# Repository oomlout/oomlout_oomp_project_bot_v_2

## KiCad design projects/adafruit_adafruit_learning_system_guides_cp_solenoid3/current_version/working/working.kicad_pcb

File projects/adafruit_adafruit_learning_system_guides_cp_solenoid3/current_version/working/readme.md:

# adafruit_learning_system_guides
 
## summary 
* id: adafruit_adafruit_learning_system_guides_cp_solenoid3
* user: adafruit
* name: adafruit_learning_system_guides
* board: cp_solenoid3
* repo: https://github.com/adafruit/Adafruit_Learning_System_Guides

* src_file_repo_sch: 
* src_file_repo_sch_link: https://github.com/adafruit/Adafruit_Learning_System_Guides/tree/main/
* full details link: https://github.com/oomlout/oomlout_oomp_project_bot_v_2/tree/main/projects/adafruit_adafruit_learning_system_guides_cp_solenoid3/current_version/working  

## schematic  
  
[schematic (pdf)](working_schematic.pdf) 

## pcb  

[board (pdf)](working.pdf)  

## working_bom
| Id | Designator | Footprint | Quantity | Designation | Supplier and ref |  | None | 
| --- | --- | --- | --- | --- | --- | --- | --- | 
| 1 | D1 | DO41-10 | 1 | 1N4004 |  |  | [''] | 
| 2 | R2 | 0414_15 | 1 | 15M |  |  | [''] | 
| 3 | SOLENOID0,LED0 | B2B-PH-K-S | 2 |  |  |  | [''] | 
| 4 | R1 | 0207_10 | 1 | 10K |  |  | [''] | 
| 5 | Q2 | TO220 | 1 | IRLB8721 |  |  | [''] | 
| 6 | C1 | C025-025X050 | 1 | 82nF |  |  | [''] | 
| 7 | MS1 | FEATHERWING_DIM | 1 | FEATHERWING_NODIM |  |  | [''] | 

## bom_schematic
| Ref | Qnty | Value | Cmp name | Footprint | Description | Vendor | DNP | 
| --- | --- | --- | --- | --- | --- | --- | --- | 
| C1 | 1 | 82nF | C-EU025-025X050 | working:C025-025X050 |  |  |  | 
| D1 | 1 | 1N4004 | 1N4004 | working:DO41-10 |  |  |  | 
| LED0 | 1 | B2B-PH-K-S | B2B-PH-K-S | working:B2B-PH-K-S |  |  |  | 
| MS1 | 1 | FEATHERWING_NODIM | FEATHERWING_NODIM | working:FEATHERWING_DIM |  |  |  | 
| Q2 | 1 | IRF510 | IRF510 | working:TO220 |  |  |  | 
| R1 | 1 | 10K | R-EU_0207/10 | working:0207_10 |  |  |  | 
| R2 | 1 | 15M | R-EU_0414/15 | working:0414_15 |  |  |  | 
| SOLENOID0 | 1 | B2B-PH-K-S | B2B-PH-K-S | working:B2B-PH-K-S |  |  |  |

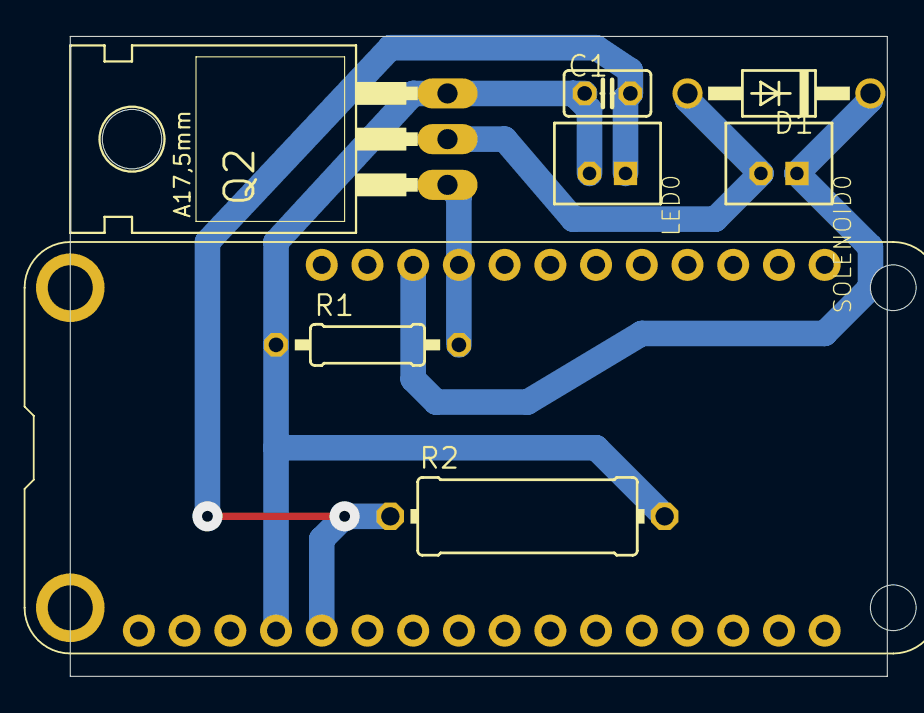
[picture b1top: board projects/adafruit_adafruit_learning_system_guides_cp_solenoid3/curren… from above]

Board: 2 copper layers, 45.4 x 35.5 mm, 8 parts (0 on the bottom side), 5 nets.

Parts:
C1: 82nF; C025-025X050
D1: 1N4004; DO41-10
LED0: B2B-PH-K-S
MS1: FEATHERWING_NODIM; FEATHERWING_DIM
Q2: IRLB8721; TO220
R1: 10K; 0207_10
R2: 15M; 0414_15
SOLENOID0: B2B-PH-K-S

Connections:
GND: C1.1, LED0.2, MS1.4, Q2.3, R1.1, R2.2
unnamed: MS1.25, Q2.1, R1.2
unnamed: D1.A, Q2.2, SOLENOID0.2
unnamed: C1.2, LED0.1, MS1.5, R2.1
USB: D1.C, MS1.26, SOLENOID0.1

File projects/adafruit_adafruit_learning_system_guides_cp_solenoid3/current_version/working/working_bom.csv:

"Id";"Designator";"Footprint";"Quantity";"Designation";"Supplier and ref";
1;"D1";"DO41-10";1;"1N4004";;;
2;"R2";"0414_15";1;"15M";;;
3;"SOLENOID0,LED0";"B2B-PH-K-S";2;"";;;
4;"R1";"0207_10";1;"10K";;;
5;"Q2";"TO220";1;"IRLB8721";;;
6;"C1";"C025-025X050";1;"82nF";;;
7;"MS1";"FEATHERWING_DIM";1;"FEATHERWING_NODIM";;;

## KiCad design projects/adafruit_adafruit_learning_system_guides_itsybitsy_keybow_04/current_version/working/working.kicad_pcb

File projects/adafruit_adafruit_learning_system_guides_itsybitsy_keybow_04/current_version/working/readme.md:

# adafruit_learning_system_guides
 
## summary 
* id: adafruit_adafruit_learning_system_guides_itsybitsy_keybow_04
* user: adafruit
* name: adafruit_learning_system_guides
* board: itsybitsy_keybow_04
* repo: https://github.com/adafruit/Adafruit_Learning_System_Guides

* src_file_repo_sch: 
* src_file_repo_sch_link: https://github.com/adafruit/Adafruit_Learning_System_Guides/tree/main/
* full details link: https://github.com/oomlout/oomlout_oomp_project_bot_v_2/tree/main/projects/adafruit_adafruit_learning_system_guides_itsybitsy_keybow_04/current_version/working  

## schematic  
  
[schematic (pdf)](working_schematic.pdf) 

## pcb  

[board (pdf)](working.pdf)  

## working_bom
| Id | Designator | Footprint | Quantity | Designation | Supplier and ref |  | None | 
| --- | --- | --- | --- | --- | --- | --- | --- | 
| 1 | JP6,JP7 | 1X14_ROUND70 | 2 |  |  |  | [''] | 
| 2 | RPI1 | PI_BONNET_NODIM | 1 | RASPBERRYPI_BPLUS_BONNETNODIM |  |  | [''] | 

## bom_schematic
| Ref | Qnty | Value | Cmp name | Footprint | Description | Vendor | DNP | 
| --- | --- | --- | --- | --- | --- | --- | --- | 
| JP6, JP7 | 2 | HEADER-1X14 | HEADER-1X14 | working:1X14_ROUND70 |  |  |  | 
| RPI1 | 1 | RASPBERRYPI_BPLUS_BONNETNODIM | RASPBERRYPI_BPLUS_BONNETNODIM | working:PI_BONNET_NODIM |  |  |  |

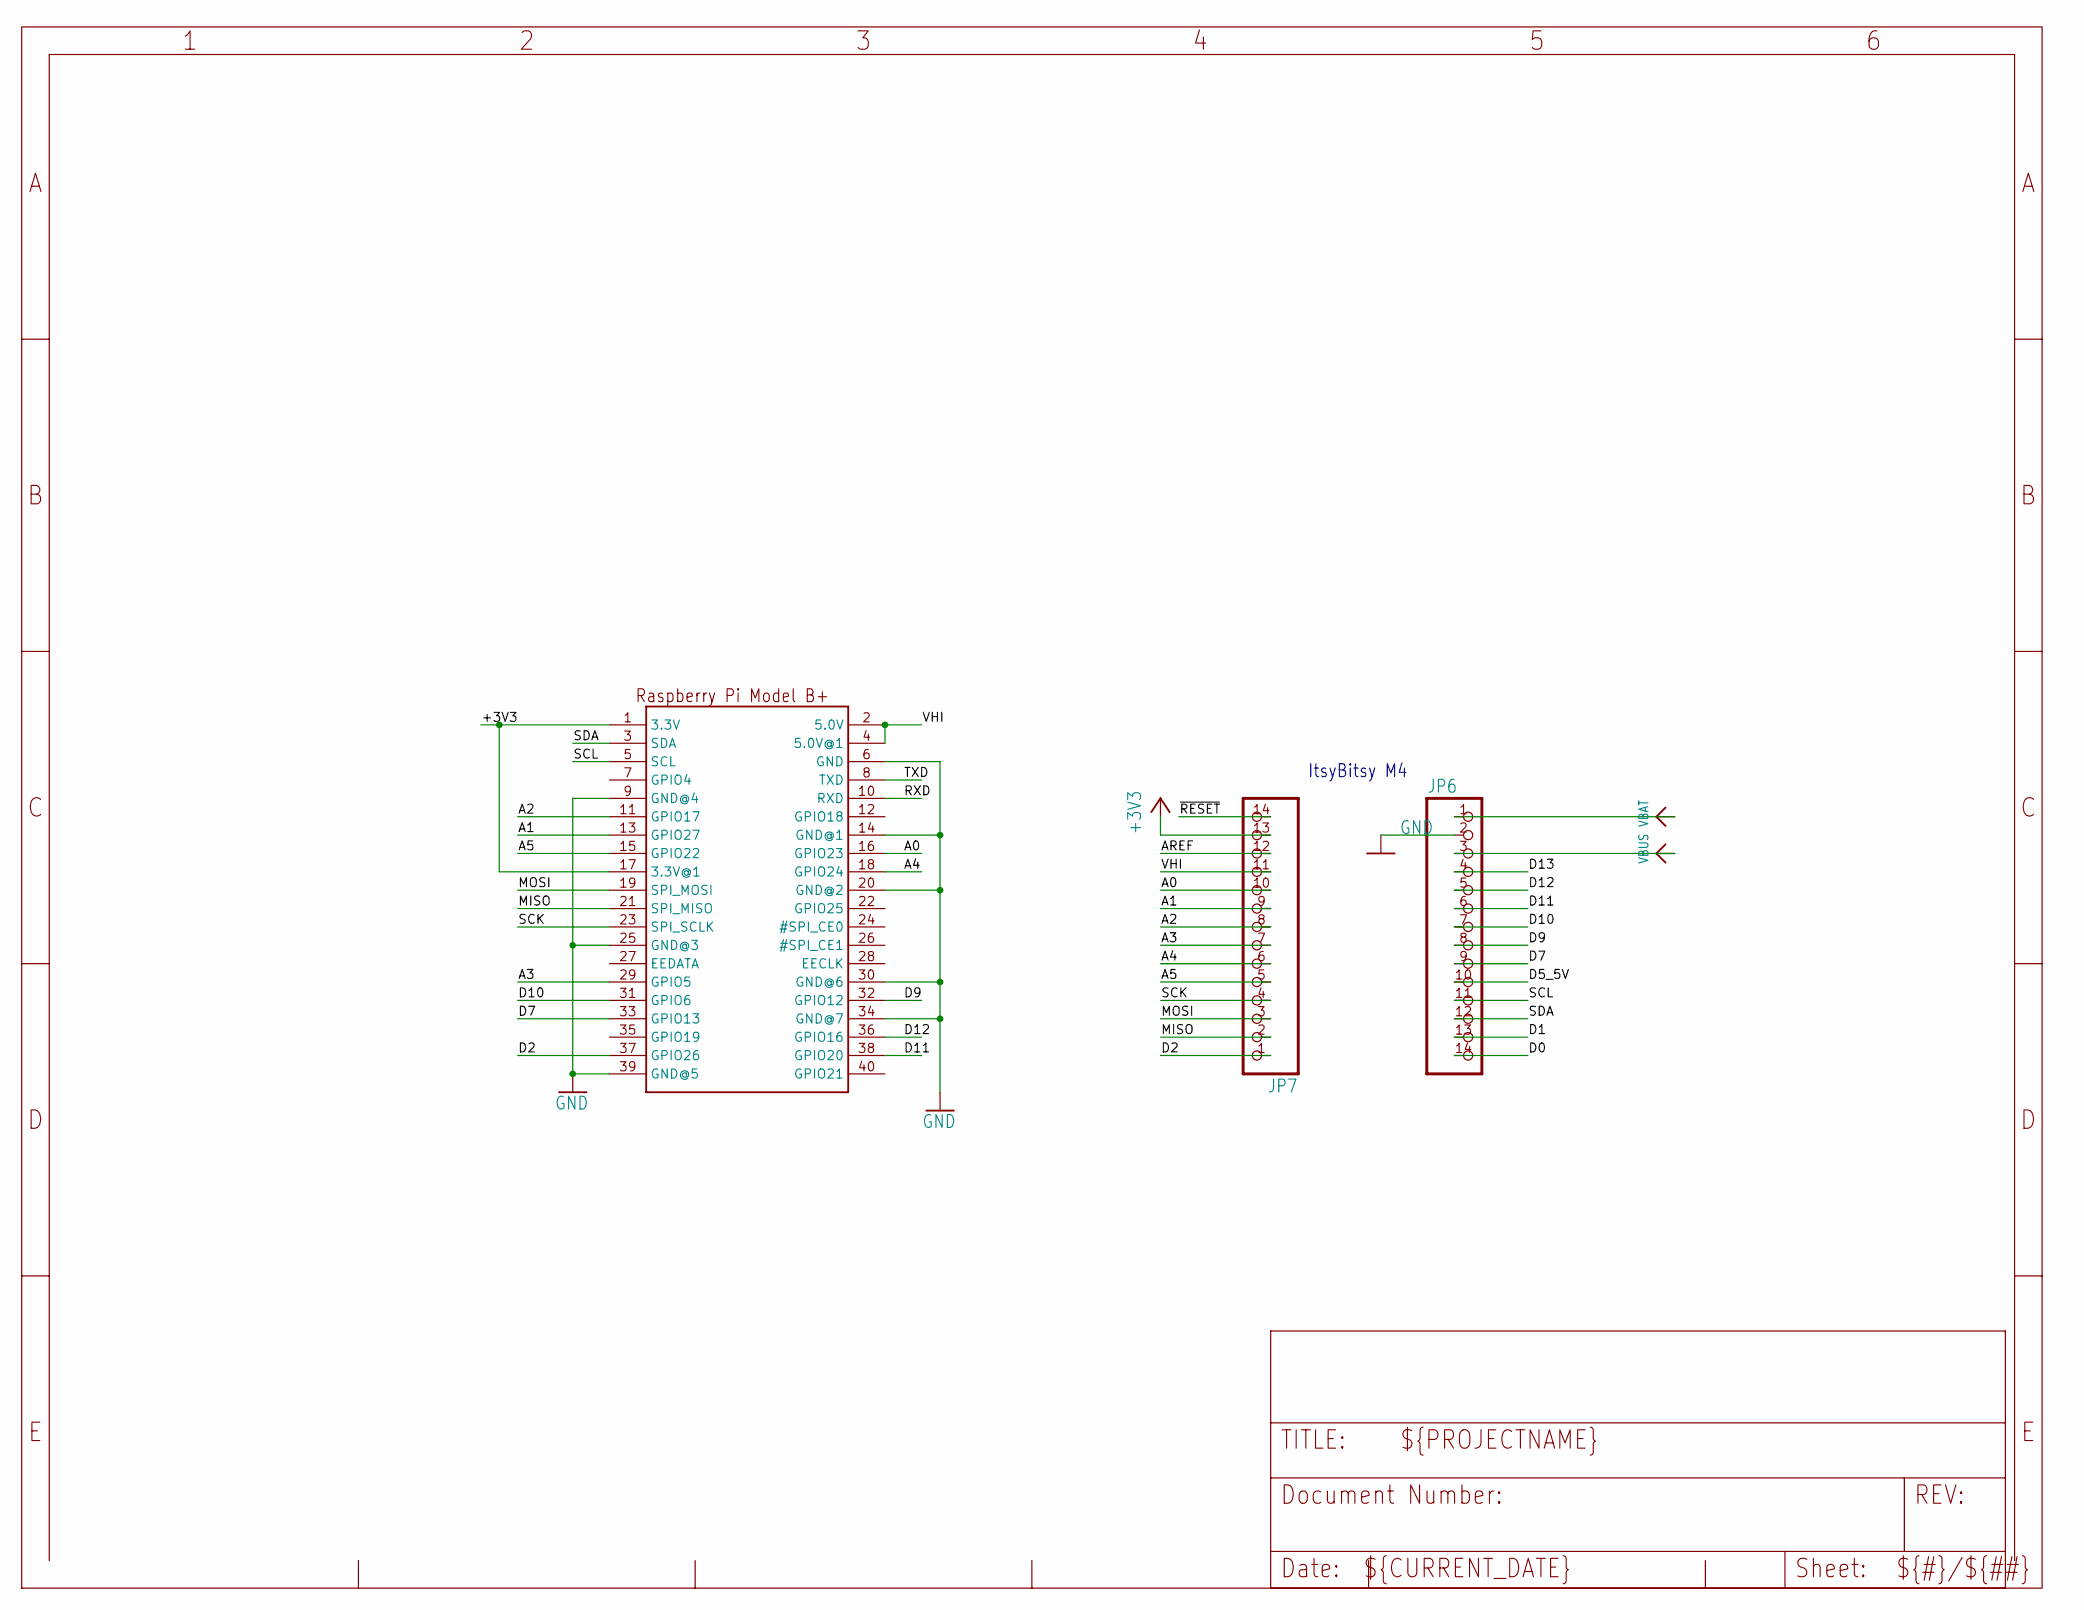
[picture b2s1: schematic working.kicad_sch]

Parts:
JP6, JP7: HEADER-1X14; 1X14_ROUND70
RPI1: RASPBERRYPI_BPLUS_BONNETNODIM; PI_BONNET_NODIM

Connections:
+3V3: JP7.13, RPI1.1 (3.3V), RPI1.17 (3.3V@1)
A0: JP7.10, RPI1.16 (GPIO23)
A1: JP7.9, RPI1.13 (GPIO27)
A2: JP7.8, RPI1.11 (GPIO17)
A3: JP7.7, RPI1.29 (GPIO5)
A4: JP7.6, RPI1.18 (GPIO24)
A5: JP7.5, RPI1.15 (GPIO22)
AREF: JP7.12
D0: JP6.14
D1: JP6.13
D2: JP7.1, RPI1.37 (GPIO26)
D5_5V: JP6.10
D7: JP6.9, RPI1.33 (GPIO13)
D9: JP6.8, RPI1.32 (GPIO12)
D10: JP6.7, RPI1.31 (GPIO6)
D11: JP6.6, RPI1.38 (GPIO20)
D12: JP6.5, RPI1.36 (GPIO16)
D13: JP6.4
GND: JP6.2, RPI1.6 (GND), RPI1.9 (GND@4), RPI1.14 (GND@1), RPI1.20 (GND@2), RPI1.25 (GND@3), RPI1.30 (GND@6), RPI1.34 (GND@7), RPI1.39 (GND@5)
MISO: JP7.2, RPI1.21 (SPI_MISO)
MOSI: JP7.3, RPI1.19 (SPI_MOSI)
RXD: RPI1.10 (RXD)
SCK: JP7.4, RPI1.23 (SPI_SCLK)
SCL: JP6.11, RPI1.5 (SCL)
SDA: JP6.12, RPI1.3 (SDA)
TXD: RPI1.8 (TXD)
VBAT: JP6.1
VBUS: JP6.3
VHI: JP7.11, RPI1.2 (5.0V), RPI1.4 (5.0V@1)
~RESET: JP7.14

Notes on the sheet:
ItsyBitsy M4

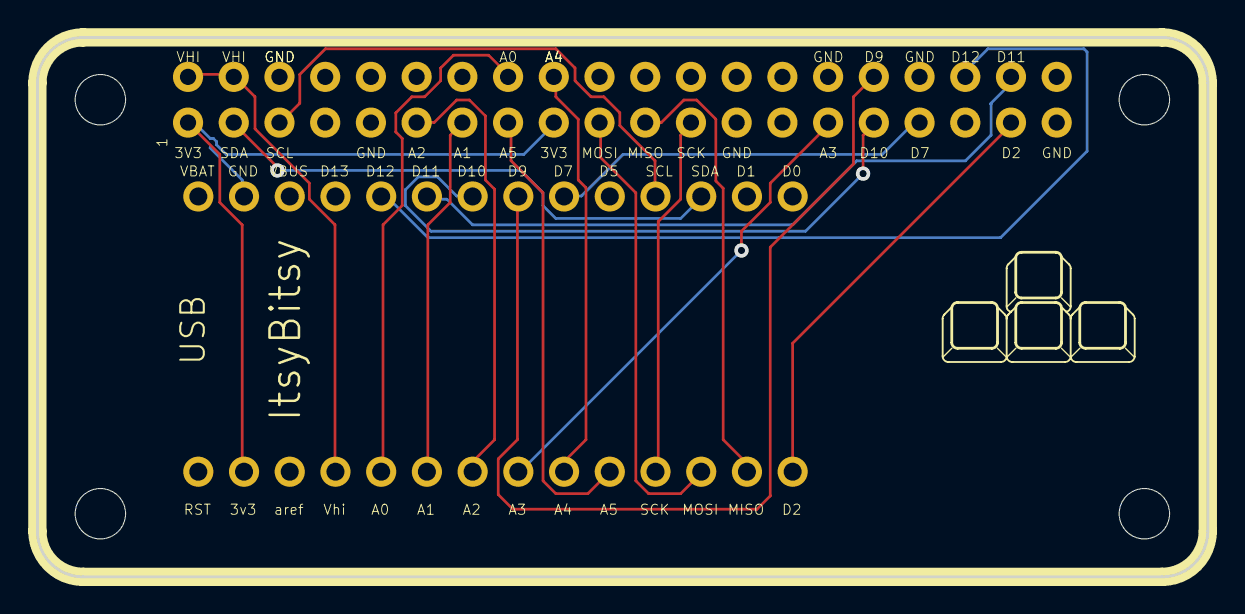
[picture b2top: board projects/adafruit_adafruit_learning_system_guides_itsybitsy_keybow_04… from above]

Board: 2 copper layers, 65.0 x 30.0 mm, 3 parts (0 on the bottom side), 20 nets.

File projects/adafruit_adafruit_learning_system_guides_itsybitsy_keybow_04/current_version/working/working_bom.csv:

"Id";"Designator";"Footprint";"Quantity";"Designation";"Supplier and ref";
1;"JP6,JP7";"1X14_ROUND70";2;"";;;
2;"RPI1";"PI_BONNET_NODIM";1;"RASPBERRYPI_BPLUS_BONNETNODIM";;;

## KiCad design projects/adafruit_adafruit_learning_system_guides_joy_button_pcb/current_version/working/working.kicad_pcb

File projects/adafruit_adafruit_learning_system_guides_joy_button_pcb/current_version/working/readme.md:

# adafruit_learning_system_guides
 
## summary 
* id: adafruit_adafruit_learning_system_guides_joy_button_pcb
* user: adafruit
* name: adafruit_learning_system_guides
* board: joy_button_pcb
* repo: https://github.com/adafruit/Adafruit_Learning_System_Guides

* src_file_repo_sch: 
* src_file_repo_sch_link: https://github.com/adafruit/Adafruit_Learning_System_Guides/tree/main/
* full details link: https://github.com/oomlout/oomlout_oomp_project_bot_v_2/tree/main/projects/adafruit_adafruit_learning_system_guides_joy_button_pcb/current_version/working  

## schematic  
  
[schematic (pdf)](working_schematic.pdf) 

## pcb  

[board (pdf)](working.pdf)  

## working_bom
| Id | Designator | Footprint | Quantity | Designation | Supplier and ref |  | None | 
| --- | --- | --- | --- | --- | --- | --- | --- | 
| 1 | S4,S2,S3,S1 | 8MM_SWITCH | 4 | SOFT_SWITCH |  |  | [''] | 
| 2 | @HOLE1,@HOLE3,@HOLE0,@HOLE2 |  | 4 |  |  |  | [''] | 
| 3 | HEADER0 | 1X06 | 1 |  |  |  | [''] | 

## bom_schematic
| Ref | Qnty | Value | Cmp name | Footprint | Description | Vendor | DNP | 
| --- | --- | --- | --- | --- | --- | --- | --- | 
| HEADER0 | 1 | PINHD-1X6 | PINHD-1X6 | working:1X06 |  |  |  | 
| S1, S2, S3, S4 | 4 | SOFT_SWITCH | SOFT_SWITCH | working:8MM_SWITCH |  |  |  |

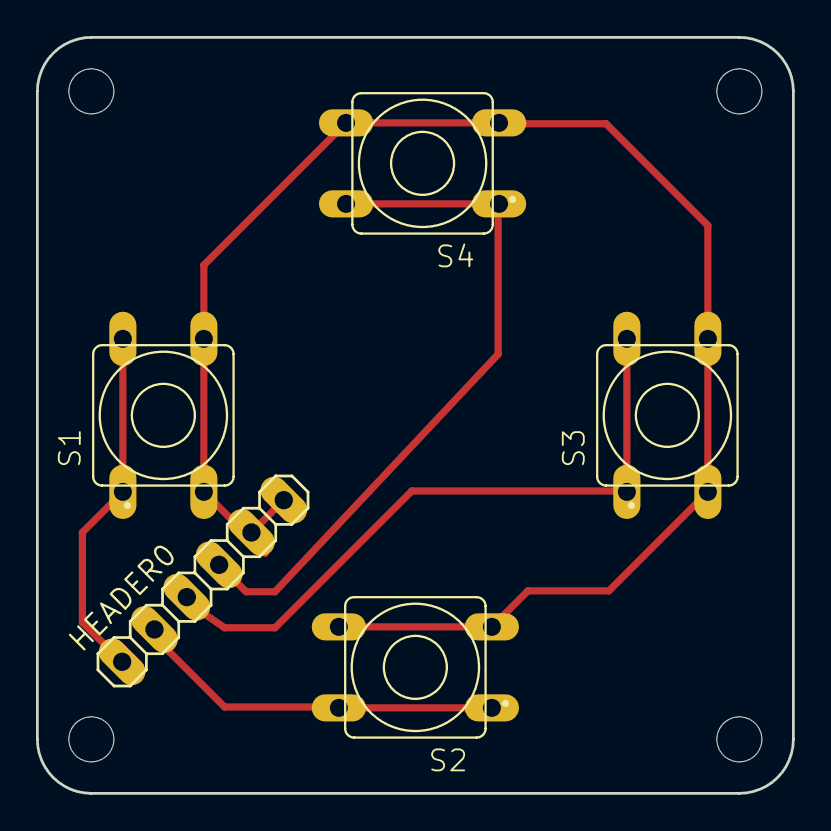
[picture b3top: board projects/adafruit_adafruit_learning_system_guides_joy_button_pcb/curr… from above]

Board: 2 copper layers, 42.0 x 42.0 mm, 9 parts (0 on the bottom side), 5 nets.

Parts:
@HOLE0, @HOLE1, @HOLE2, @HOLE3: (no value)
HEADER0: 1X06
S1, S2, S3, S4: SOFT_SWITCH; 8MM_SWITCH

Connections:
A: HEADER0.1, S1.1, S1.2
B: HEADER0.2, S2.1, S2.2
GND: HEADER0.5, HEADER0.6, S1.3, S1.4, S2.3, S2.4, S3.3, S3.4, S4.3, S4.4
X: HEADER0.3, S3.1, S3.2
Y: HEADER0.4, S4.1, S4.2

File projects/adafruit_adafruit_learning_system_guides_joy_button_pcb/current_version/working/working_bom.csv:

"Id";"Designator";"Footprint";"Quantity";"Designation";"Supplier and ref";
1;"S4,S2,S3,S1";"8MM_SWITCH";4;"SOFT_SWITCH";;;
2;"@HOLE1,@HOLE3,@HOLE0,@HOLE2";"";4;"";;;
3;"HEADER0";"1X06";1;"";;;

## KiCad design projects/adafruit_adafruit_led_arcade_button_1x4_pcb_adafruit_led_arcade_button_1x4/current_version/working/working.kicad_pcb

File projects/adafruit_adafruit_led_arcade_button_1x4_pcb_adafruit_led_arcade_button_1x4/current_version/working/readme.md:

# adafruit_led_arcade_button_1x4_pcb
 
## summary 
* id: adafruit_adafruit_led_arcade_button_1x4_pcb_adafruit_led_arcade_button_1x4
* user: adafruit
* name: adafruit_led_arcade_button_1x4_pcb
* board: adafruit_led_arcade_button_1x4
* repo: https://github.com/adafruit/Adafruit-LED-Arcade-Button-1x4-PCB

* src_file_repo_sch: 
* src_file_repo_sch_link: https://github.com/adafruit/Adafruit-LED-Arcade-Button-1x4-PCB/tree/main/
* full details link: https://github.com/oomlout/oomlout_oomp_project_bot_v_2/tree/main/projects/adafruit_adafruit_led_arcade_button_1x4_pcb_adafruit_led_arcade_button_1x4/current_version/working  

## schematic  
  
[schematic (pdf)](working_schematic.pdf) 

## pcb  

[board (pdf)](working.pdf)  

## working_bom
| Id | Designator | Footprint | Quantity | Designation | Supplier and ref |  | None | 
| --- | --- | --- | --- | --- | --- | --- | --- | 
| 1 | C3,C2,C9,C8 | 0805-NO | 4 | 10uF |  |  | [''] | 
| 2 | R4,R2,R6,R5 | 0603-NO | 4 | 100 |  |  | [''] | 
| 3 | IC1 | SOT23-6 | 1 | AP3602 |  |  | [''] | 
| 4 | TP9,TP3,TP1,TP6,TP8,TP5,TP4,TP2,TP7 | TESTPOINT_ROUND_1.5MM | 9 |  |  |  | [''] | 
| 5 | R1,R7,R8,R3 | 0603-NO | 4 | 10K |  |  | [''] | 
| 6 | SJ4,SJ3,SJ2,SJ5,SJ1 | SOLDERJUMPER_CLOSEDWIRE | 5 |  |  |  | [''] | 
| 7 | U$30,U$31,U$53 | STEMMAQT | 3 |  |  |  | [''] | 
| 8 | R9 | RESPACK_4X0603 | 1 | 10K |  |  | [''] | 
| 9 | CONN3,CONN4 | JST_SH4 | 2 | STEMMA_I2C_QT |  |  | [''] | 
| 10 | C4 | 0603-NO | 1 | 0.1uF |  |  | [''] | 
| 11 | C10 | 0805-NO | 1 | 1uF |  |  | [''] | 
| 12 | FID2,FID1,FID4,FID3 | FIDUCIAL_1MM | 4 | FIDUCIAL_1MM |  |  | [''] | 
| 13 | U$3,U$21,U$17,U$19 | MOUNTINGHOLE_2.5_PLATED | 4 | MOUNTINGHOLE2.5 |  |  | [''] | 
| 14 | Q3,Q1 | SOT363 | 2 | BSS138 |  |  | [''] | 
| 15 | IC2 | QFN24_4MM | 1 | ATTINY8X7-MU |  |  | [''] | 
| 16 | JP1,JP5 | 1X06_ROUND_70 | 2 |  |  |  | [''] | 
| 17 | D2 | CHIPLED_0603_NOOUTLINE | 1 | GREEN |  |  | [''] | 
| 18 | U$9,U$2,U$52 | ADAFRUIT_3.5MM | 3 |  |  |  | [''] | 
| 19 | U$25 | PCBFEAT-REV-040 | 1 |  |  |  | [''] | 
| 20 | X7,X8,X2,X1,X3,X6,X5,X4 | JST-XH-2-SV | 8 | CON_JST_XH_2PIN-VERT |  |  | [''] | 
| 21 | U$24,U$20,U$23,U$50,U$15,U$16,U$7,U$26 | SYMBOL_PLUS | 8 |  |  |  | [''] | 
| 22 | U$8,U$47,U$49,U$48,U$45,U$14,U$1,U$46 | SYMBOL_MINUS | 8 |  |  |  | [''] | 

## bom_schematic
| Ref | Qnty | Value | Cmp name | Footprint | Description | Vendor | DNP | 
| --- | --- | --- | --- | --- | --- | --- | --- | 
| C2, C3, C8, C9 | 4 | 10uF | CAP_CERAMIC0805-NOOUTLINE | working:0805-NO |  |  |  | 
| C4 | 1 | 0.1uF | CAP_CERAMIC0603_NO | working:0603-NO |  |  |  | 
| C10 | 1 | 1uF | CAP_CERAMIC0805-NOOUTLINE | working:0805-NO |  |  |  | 
| CONN3, CONN4 | 2 | STEMMA_I2C_QT | STEMMA_I2C_QT | working:JST_SH4 |  |  |  | 
| D2 | 1 | GREEN | LED0603_NOOUTLINE | working:CHIPLED_0603_NOOUTLINE |  |  |  | 
| FID1, FID2, FID3, FID4 | 4 | FIDUCIAL_1MM | FIDUCIAL_1MM | working:FIDUCIAL_1MM |  |  |  | 
| IC1 | 1 | AP3602 | AP3602 | working:SOT23-6 |  |  |  | 
| IC2 | 1 | ATTINY8X7-MU | ATTINY8X7-MU | working:QFN24_4MM |  |  |  | 
| JP1, JP5 | 2 | HEADER-1X670MIL | HEADER-1X670MIL | working:1X06_ROUND_70 |  |  |  | 
| Q1, Q3 | 2 | BSS138 | MOSFET-N_DUAL | working:SOT363 |  |  |  | 
| R1, R3, R7, R8 | 4 | 10K | RESISTOR_0603_NOOUT | working:0603-NO |  |  |  | 
| R2, R4, R5, R6 | 4 | 100 | RESISTOR_0603_NOOUT | working:0603-NO |  |  |  | 
| R9 | 1 | 10K | RESISTOR_4PACK | working:RESPACK_4X0603 |  |  |  | 
| SJ1, SJ2, SJ3, SJ4, SJ5 | 5 | SOLDERJUMPERCLOSED | SOLDERJUMPERCLOSED | working:SOLDERJUMPER_CLOSEDWIRE |  |  |  | 
| TP1, TP2, TP3, TP4, TP5, TP6, TP7, TP8, TP9 | 9 | TESTPOINTROUND1.5MM | TESTPOINTROUND1.5MM | working:TESTPOINT_ROUND_1.5MM |  |  |  | 
| U$3, U$17, U$19, U$21 | 4 | MOUNTINGHOLE2.5 | MOUNTINGHOLE2.5 | working:MOUNTINGHOLE_2.5_PLATED |  |  |  | 
| X1, X2, X3, X4, X5, X6, X7, X8 | 8 | CON_JST_XH_2PIN-VERT | CON_JST_XH_2PIN-VERT | working:JST-XH-2-SV |  |  |  | 

## mounting_holes
| x | y | package | value | ref | size | 
| --- | --- | --- | --- | --- | --- | 
| 38.1 | 16.51 | MOUNTINGHOLE_2.5_PLATED | MOUNTINGHOLE2.5 | U$3 | m3 | 
| 0.0 | 16.51 | MOUNTINGHOLE_2.5_PLATED | MOUNTINGHOLE2.5 | U$17 | m3 | 
| 38.1 | 0.0 | MOUNTINGHOLE_2.5_PLATED | MOUNTINGHOLE2.5 | U$19 | m3 | 
| 0.0 | 0.0 | MOUNTINGHOLE_2.5_PLATED | MOUNTINGHOLE2.5 | U$21 | m3 |

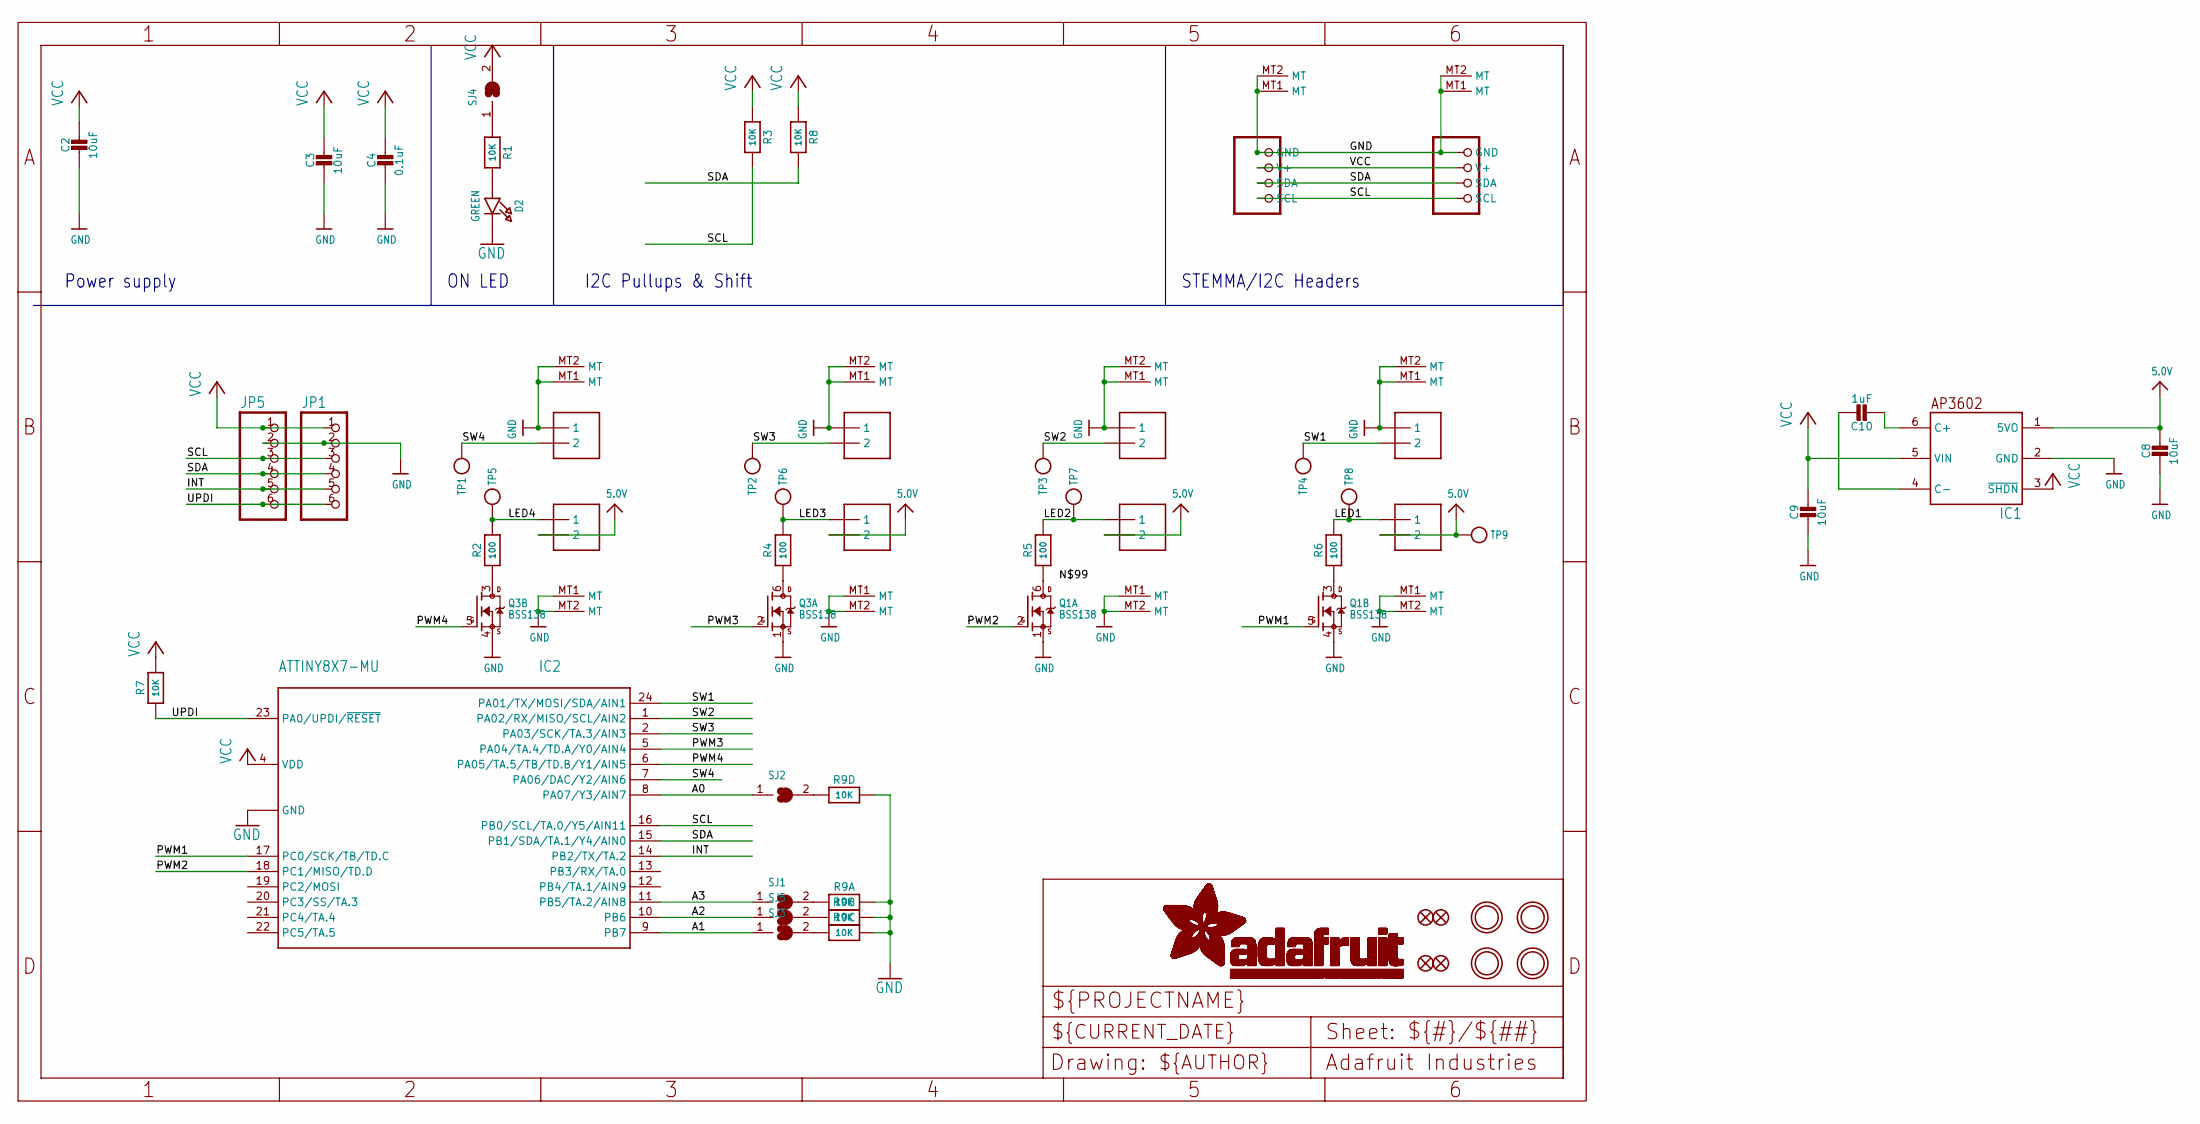
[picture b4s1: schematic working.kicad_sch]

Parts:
C2, C3, C8, C9: 10uF; 0805-NO
C4: 0.1uF; 0603-NO
C10: 1uF; 0805-NO
CONN3, CONN4: STEMMA_I2C_QT; JST_SH4
D2: GREEN; CHIPLED_0603_NOOUTLINE
FID1, FID2, FID3, FID4: FIDUCIAL_1MM
IC1: AP3602; SOT23-6
IC2: ATTINY8X7-MU; QFN24_4MM
JP1, JP5: HEADER-1X670MIL; 1X06_ROUND_70
Q1, Q3: BSS138; SOT363
R1, R3, R7, R8: 10K; 0603-NO
R2, R4, R5, R6: 100; 0603-NO
R9: 10K; RESPACK_4X0603
SJ1, SJ2, SJ3, SJ4, SJ5: SOLDERJUMPERCLOSED; SOLDERJUMPER_CLOSEDWIRE
TP1, TP2, TP3, TP4, TP5, TP6, TP7, TP8, TP9: TESTPOINTROUND1.5MM; TESTPOINT_ROUND_1.5MM
U$3, U$17, U$19, U$21: MOUNTINGHOLE2.5; MOUNTINGHOLE_2.5_PLATED
X1, X2, X3, X4, X5, X6, X7, X8: CON_JST_XH_2PIN-VERT; JST-XH-2-SV

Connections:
5.0V: C8.1, IC1.1 (5VO), TP9.P$1, X2.2, X4.2, X6.2, X8.2
A0: IC2.8 (PA07/Y3/AIN7), SJ2.1
A1: IC2.9 (PB7), SJ3.1
A2: IC2.10 (PB6), SJ5.1
A3: IC2.11 (PB5/TA.2/AIN8), SJ1.1
GND: C2.2, C3.2, C4.2, C8.2, C9.2, CONN3.1 (GND), CONN3.MT1 (MT), CONN3.MT2 (MT), CONN4.1 (GND), CONN4.MT1 (MT), CONN4.MT2 (MT), D2.C, IC1.2 (GND), IC2.3 (GND), IC2.THERM (GND), JP1.2, JP5.2, Q1.1 (S), Q1.4 (S), Q3.1 (S), Q3.4 (S), R9.5 (2), R9.6 (2), R9.7 (2), R9.8 (2), X1.1, X1.MT1 (MT), X1.MT2 (MT), X2.MT1 (MT), X2.MT2 (MT), X3.1, X3.MT1 (MT), X3.MT2 (MT), X4.MT1 (MT), X4.MT2 (MT), X5.1, X5.MT1 (MT), X5.MT2 (MT), X6.MT1 (MT), X6.MT2 (MT), X7.1, X7.MT1 (MT), X7.MT2 (MT), X8.MT1 (MT), X8.MT2 (MT)
INT: IC2.14 (PB2/TX/TA.2), JP1.5, JP5.5
LED1: R6.2, TP8.P$1, X8.1
LED2: R5.2, TP7.P$1, X6.1
LED3: R4.2, TP6.P$1, X4.1
LED4: R2.2, TP5.P$1, X2.1
unnamed: D2.A, R1.2
unnamed: C10.2, IC1.6 (C+)
unnamed: C10.1, IC1.4 (C-)
unnamed: Q3.6 (D), R4.1
unnamed: R1.1, SJ4.1
unnamed: R9.1, SJ1.2
unnamed: R9.2 (1), SJ5.2
unnamed: R9.3 (1), SJ3.2
unnamed: Q1.3 (D), R6.1
unnamed: Q3.3 (D), R2.1
unnamed: R9.4 (1), SJ2.2
unnamed: Q1.6 (D), R5.1
PWM1: IC2.17 (PC0/SCK/TB/TD.C), Q1.5 (G)
PWM2: IC2.18 (PC1/MISO/TD.D), Q1.2 (G)
PWM3: IC2.5 (PA04/TA.4/TD.A/Y0/AIN4), Q3.2 (G)
PWM4: IC2.6 (PA05/TA.5/TB/TD.B/Y1/AIN5), Q3.5 (G)
SCL: CONN3.4 (SCL), CONN4.4 (SCL), IC2.16 (PB0/SCL/TA.0/Y5/AIN11), JP1.3, JP5.3, R3.2
SDA: CONN3.3 (SDA), CONN4.3 (SDA), IC2.15 (PB1/SDA/TA.1/Y4/AIN0), JP1.4, JP5.4, R8.2
SW1: IC2.24 (PA01/TX/MOSI/SDA/AIN1), TP4.P$1, X7.2
SW2: IC2.1 (PA02/RX/MISO/SCL/AIN2), TP3.P$1, X5.2
SW3: IC2.2 (PA03/SCK/TA.3/AIN3), TP2.P$1, X3.2
SW4: IC2.7 (PA06/DAC/Y2/AIN6), TP1.P$1, X1.2
UPDI: IC2.23 (PA0/UPDI/~RESET), JP1.6, JP5.6, R7.1
VCC: C2.1, C3.1, C4.1, C9.1, CONN3.2 (V+), CONN4.2 (V+), IC1.3 (~SHDN), IC1.5 (VIN), IC2.4 (VDD), JP1.1, JP5.1, R3.1, R7.2, R8.1, SJ4.2

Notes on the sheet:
ON LED
I2C Pullups & Shift
Power supply
STEMMA/I2C Headers

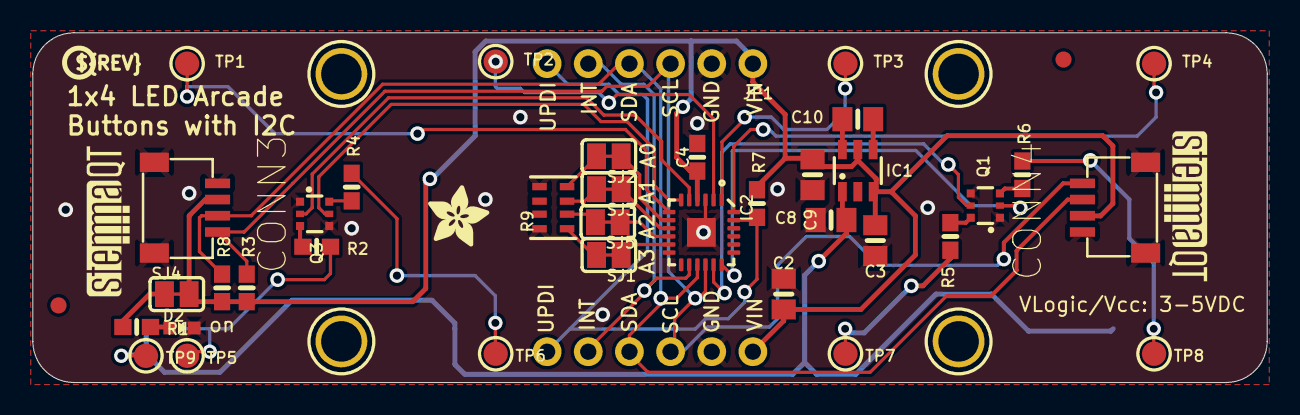
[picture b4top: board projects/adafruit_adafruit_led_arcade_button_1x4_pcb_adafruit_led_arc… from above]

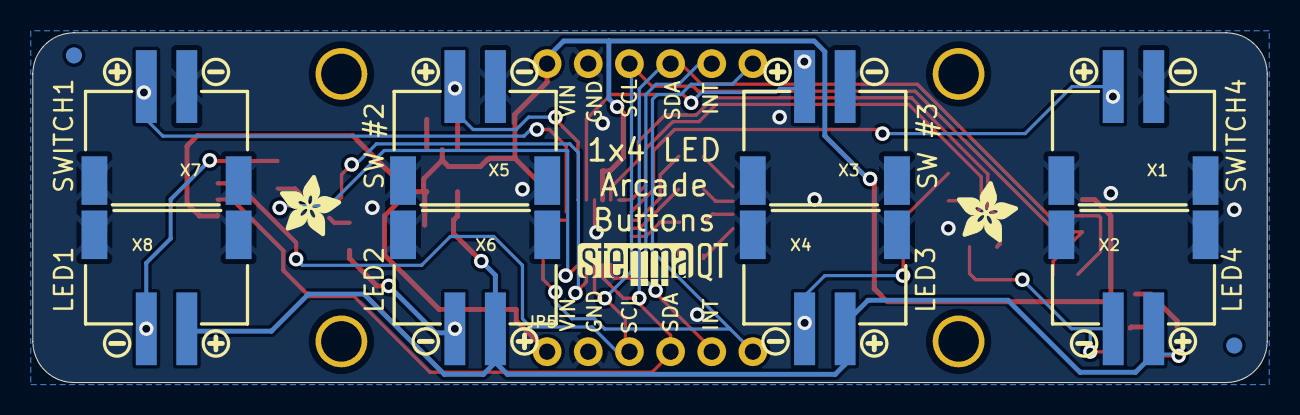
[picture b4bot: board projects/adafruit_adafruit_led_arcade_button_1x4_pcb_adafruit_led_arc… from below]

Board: 2 copper layers, 76.2 x 21.6 mm, 77 parts (30 on the bottom side), 35 nets.

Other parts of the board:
U$1, U$8, U$14, U$45, U$46, U$47, U$48, U$49: SYMBOL_MINUS
U$2, U$9, U$52: ADAFRUIT_3.5MM
U$7, U$15, U$16, U$20, U$23, U$24, U$26, U$50: SYMBOL_PLUS
U$25: PCBFEAT-REV-040
U$30, U$31, U$53: STEMMAQT

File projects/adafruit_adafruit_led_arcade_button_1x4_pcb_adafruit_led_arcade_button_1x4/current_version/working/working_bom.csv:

"Id";"Designator";"Footprint";"Quantity";"Designation";"Supplier and ref";
1;"C3,C2,C9,C8";"0805-NO";4;"10uF";;;
2;"R4,R2,R6,R5";"0603-NO";4;"100";;;
3;"IC1";"SOT23-6";1;"AP3602";;;
4;"TP9,TP3,TP1,TP6,TP8,TP5,TP4,TP2,TP7";"TESTPOINT_ROUND_1.5MM";9;"";;;
5;"R1,R7,R8,R3";"0603-NO";4;"10K";;;
6;"SJ4,SJ3,SJ2,SJ5,SJ1";"SOLDERJUMPER_CLOSEDWIRE";5;"";;;
7;"U$30,U$31,U$53";"STEMMAQT";3;"";;;
8;"R9";"RESPACK_4X0603";1;"10K";;;
9;"CONN3,CONN4";"JST_SH4";2;"STEMMA_I2C_QT";;;
10;"C4";"0603-NO";1;"0.1uF";;;
11;"C10";"0805-NO";1;"1uF";;;
12;"FID2,FID1,FID4,FID3";"FIDUCIAL_1MM";4;"FIDUCIAL_1MM";;;
13;"U$3,U$21,U$17,U$19";"MOUNTINGHOLE_2.5_PLATED";4;"MOUNTINGHOLE2.5";;;
14;"Q3,Q1";"SOT363";2;"BSS138";;;
15;"IC2";"QFN24_4MM";1;"ATTINY8X7-MU";;;
16;"JP1,JP5";"1X06_ROUND_70";2;"";;;
17;"D2";"CHIPLED_0603_NOOUTLINE";1;"GREEN";;;
18;"U$9,U$2,U$52";"ADAFRUIT_3.5MM";3;"";;;
19;"U$25";"PCBFEAT-REV-040";1;"";;;
20;"X7,X8,X2,X1,X3,X6,X5,X4";"JST-XH-2-SV";8;"CON_JST_XH_2PIN-VERT";;;
21;"U$24,U$20,U$23,U$50,U$15,U$16,U$7,U$26";"SYMBOL_PLUS";8;"";;;
22;"U$8,U$47,U$49,U$48,U$45,U$14,U$1,U$46";"SYMBOL_MINUS";8;"";;;

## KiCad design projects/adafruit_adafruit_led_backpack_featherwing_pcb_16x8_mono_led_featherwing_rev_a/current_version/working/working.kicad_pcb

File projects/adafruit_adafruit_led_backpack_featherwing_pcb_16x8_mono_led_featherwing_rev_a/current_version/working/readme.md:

# adafruit_led_backpack_featherwing_pcb
 
## summary 
* id: adafruit_adafruit_led_backpack_featherwing_pcb_16x8_mono_led_featherwing_rev_a
* user: adafruit
* name: adafruit_led_backpack_featherwing_pcb
* board: 16x8_mono_led_featherwing_rev_a
* repo: https://github.com/adafruit/Adafruit-LED-Backpack-FeatherWing-PCB

* src_file_repo_sch: 
* src_file_repo_sch_link: https://github.com/adafruit/Adafruit-LED-Backpack-FeatherWing-PCB/tree/master/
* full details link: https://github.com/oomlout/oomlout_oomp_project_bot_v_2/tree/main/projects/adafruit_adafruit_led_backpack_featherwing_pcb_16x8_mono_led_featherwing_rev_a/current_version/working  

## schematic  
  
[schematic (pdf)](working_schematic.pdf) 

## pcb  

[board (pdf)](working.pdf)  

## working_bom
| Id | Designator | Footprint | Quantity | Designation | Supplier and ref |  | None | 
| --- | --- | --- | --- | --- | --- | --- | --- | 
| 1 | C2,C1,C3 | 0805-NO | 3 | 10uF |  |  | [''] | 
| 2 | FID2,FID1 | FIDUCIAL_1MM | 2 | FIDUCIAL" |  |  | [''] | 
| 3 | A0,A2,A1 | SOLDERJUMPER_REFLOW_NOPASTE | 3 |  |  |  | [''] | 
| 4 | U2 | SOP28_300MIL_SKINNY | 1 | 28-SOIC |  |  | [''] | 
| 5 | R2,R1 | 0805-NO | 2 | 10K |  |  | [''] | 
| 6 | R4,R5,R3 | 0805-NO | 3 | 47K |  |  | [''] | 
| 7 | D1 | SOD-323F | 1 | 1N4148 |  |  | [''] | 
| 8 | U$2 | ADAFRUIT_5MM | 1 |  |  |  | [''] | 
| 9 | U$1 | FEATHERLOGO_SMALL | 1 |  |  |  | [''] | 
| 10 | LED2,LED1 | SEGMENT_BL-M07C881UR | 2 |  |  |  | [''] | 
| 11 | MS1 | FEATHERWING | 1 | FEATHERWING |  |  | [''] | 

## bom_schematic
| Ref | Qnty | Value | Cmp name | Footprint | Description | Vendor | DNP | 
| --- | --- | --- | --- | --- | --- | --- | --- | 
| A0, A1, A2 | 3 | SOLDERJUMPERREFLOW_NOPASTE | SOLDERJUMPERREFLOW_NOPASTE | working:SOLDERJUMPER_REFLOW_NOPASTE |  |  |  | 
| C1, C2, C3 | 3 | 10uF | CAP_CERAMIC0805-NOOUTLINE | working:0805-NO |  |  |  | 
| D1 | 1 | 1N4148 | DIODESOD-323F | working:SOD-323F |  |  |  | 
| FID1, FID2 | 2 | FIDUCIAL"" | FIDUCIAL{dblquote}{dblquote} | working:FIDUCIAL_1MM |  |  |  | 
| LED1, LED2 | 2 | DISP_SEGMENT_8X8_ROWCATHODE | DISP_SEGMENT_8X8_ROWCATHODE | working:SEGMENT_BL-M07C881UR |  |  |  | 
| MS1 | 1 | FEATHERWING | FEATHERWING | working:FEATHERWING |  |  |  | 
| R1, R2 | 2 | 10K | RESISTOR0805_NOOUTLINE | working:0805-NO |  |  |  | 
| R3, R4, R5 | 3 | 47K | RESISTOR0805_NOOUTLINE | working:0805-NO |  |  |  | 
| U2 | 1 | 28-SOIC | HT16K33_SOP28_SKINNY | working:SOP28_300MIL_SKINNY |  |  |  |

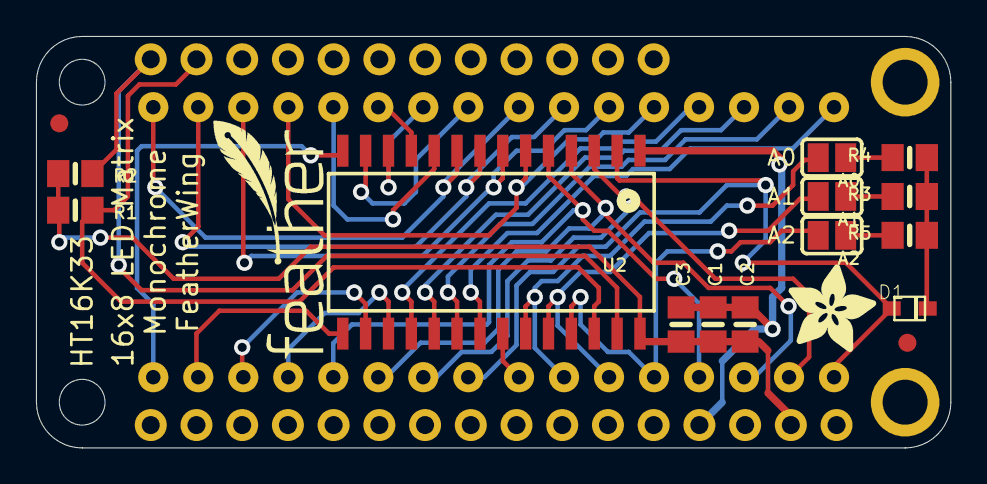
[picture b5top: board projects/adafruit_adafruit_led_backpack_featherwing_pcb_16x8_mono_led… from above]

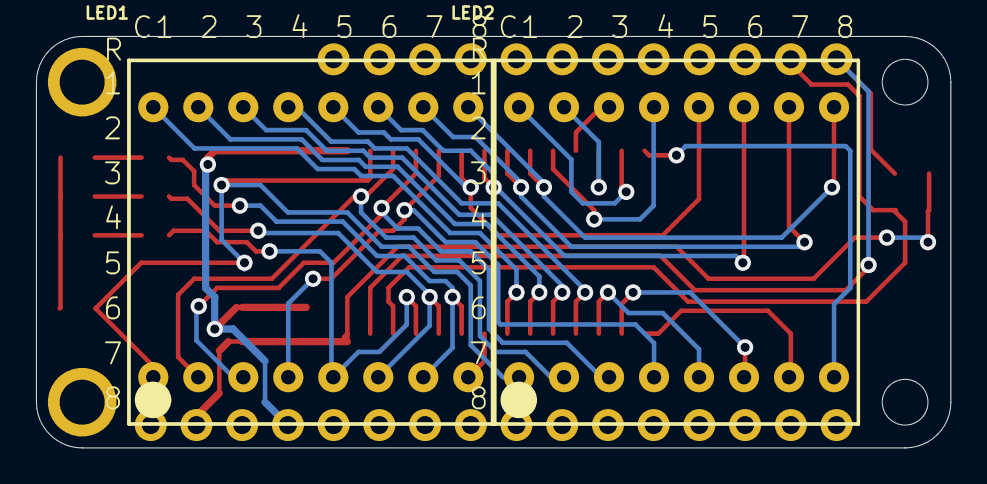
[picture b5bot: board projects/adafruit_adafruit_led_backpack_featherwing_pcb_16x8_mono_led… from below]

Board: 2 copper layers, 50.8 x 22.9 mm, 20 parts (3 on the bottom side), 32 nets.

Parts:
A0, A1, A2: SOLDERJUMPER_REFLOW_NOPASTE
C1, C2, C3: 10uF; 0805-NO
D1: 1N4148; SOD-323F
FID1, FID2: FIDUCIAL""; FIDUCIAL_1MM
LED1, LED2: SEGMENT_BL-M07C881UR
MS1: FEATHERWING
R1, R2: 10K; 0805-NO
R3, R4, R5: 47K; 0805-NO
U2: 28-SOIC; SOP28_300MIL_SKINNY
U$1: FEATHERLOGO_SMALL
U$2: ADAFRUIT_5MM

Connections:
A0: A0.2, LED1.7, U2.P$23
A1: A1.2, LED1.6, U2.P$24
A2: A2.2, LED1.5, U2.P$25
GND: C1.2, C2.2, C3.2, MS1.4, U2.P$1
unnamed: LED1.9, LED2.9, U2.P$9
unnamed: LED1.10, LED2.10, U2.P$8
unnamed: LED1.11, LED2.11, U2.P$7
unnamed: LED1.12, LED2.12, U2.P$6
unnamed: LED1.4, LED2.4, U2.P$5
unnamed: LED1.3, LED2.3, U2.P$4
unnamed: LED1.2, LED2.2, U2.P$3
unnamed: D1.A, LED1.1, LED2.1, U2.P$2
unnamed: A2.1, R5.2
unnamed: LED2.14, U2.P$11
unnamed: LED2.15, U2.P$12
unnamed: LED2.13, U2.P$10
unnamed: D1.C, R3.1, R4.1, R5.1
unnamed: A1.1, R3.2
unnamed: A0.1, R4.2
unnamed: LED1.13, U2.P$18
unnamed: LED1.14, U2.P$19
unnamed: LED1.16, U2.P$21
unnamed: LED1.8, U2.P$22
unnamed: LED1.15, U2.P$20
unnamed: LED2.5, U2.P$17
unnamed: LED2.6, U2.P$16
unnamed: LED2.8, U2.P$14
unnamed: LED2.7, U2.P$15
unnamed: LED2.16, U2.P$13
SCL: MS1.18, R1.2, U2.P$26
SDA: MS1.17, R2.2, U2.P$27
VDD: C1.1, C2.1, C3.1, MS1.2, R1.1, R2.1, U2.P$28

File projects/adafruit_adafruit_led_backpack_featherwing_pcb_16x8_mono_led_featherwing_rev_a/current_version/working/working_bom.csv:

"Id";"Designator";"Footprint";"Quantity";"Designation";"Supplier and ref";
1;"C2,C1,C3";"0805-NO";3;"10uF";;;
2;"FID2,FID1";"FIDUCIAL_1MM";2;"FIDUCIAL""";;;
3;"A0,A2,A1";"SOLDERJUMPER_REFLOW_NOPASTE";3;"";;;
4;"U2";"SOP28_300MIL_SKINNY";1;"28-SOIC";;;
5;"R2,R1";"0805-NO";2;"10K";;;
6;"R4,R5,R3";"0805-NO";3;"47K";;;
7;"D1";"SOD-323F";1;"1N4148";;;
8;"U$2";"ADAFRUIT_5MM";1;"";;;
9;"U$1";"FEATHERLOGO_SMALL";1;"";;;
10;"LED2,LED1";"SEGMENT_BL-M07C881UR";2;"";;;
11;"MS1";"FEATHERWING";1;"FEATHERWING";;;
